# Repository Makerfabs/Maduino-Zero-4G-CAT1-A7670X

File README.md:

# Maduino-Zero-4G-CAT1-A7670X
Maduino Zero 4G LTE CAT1 A7670X

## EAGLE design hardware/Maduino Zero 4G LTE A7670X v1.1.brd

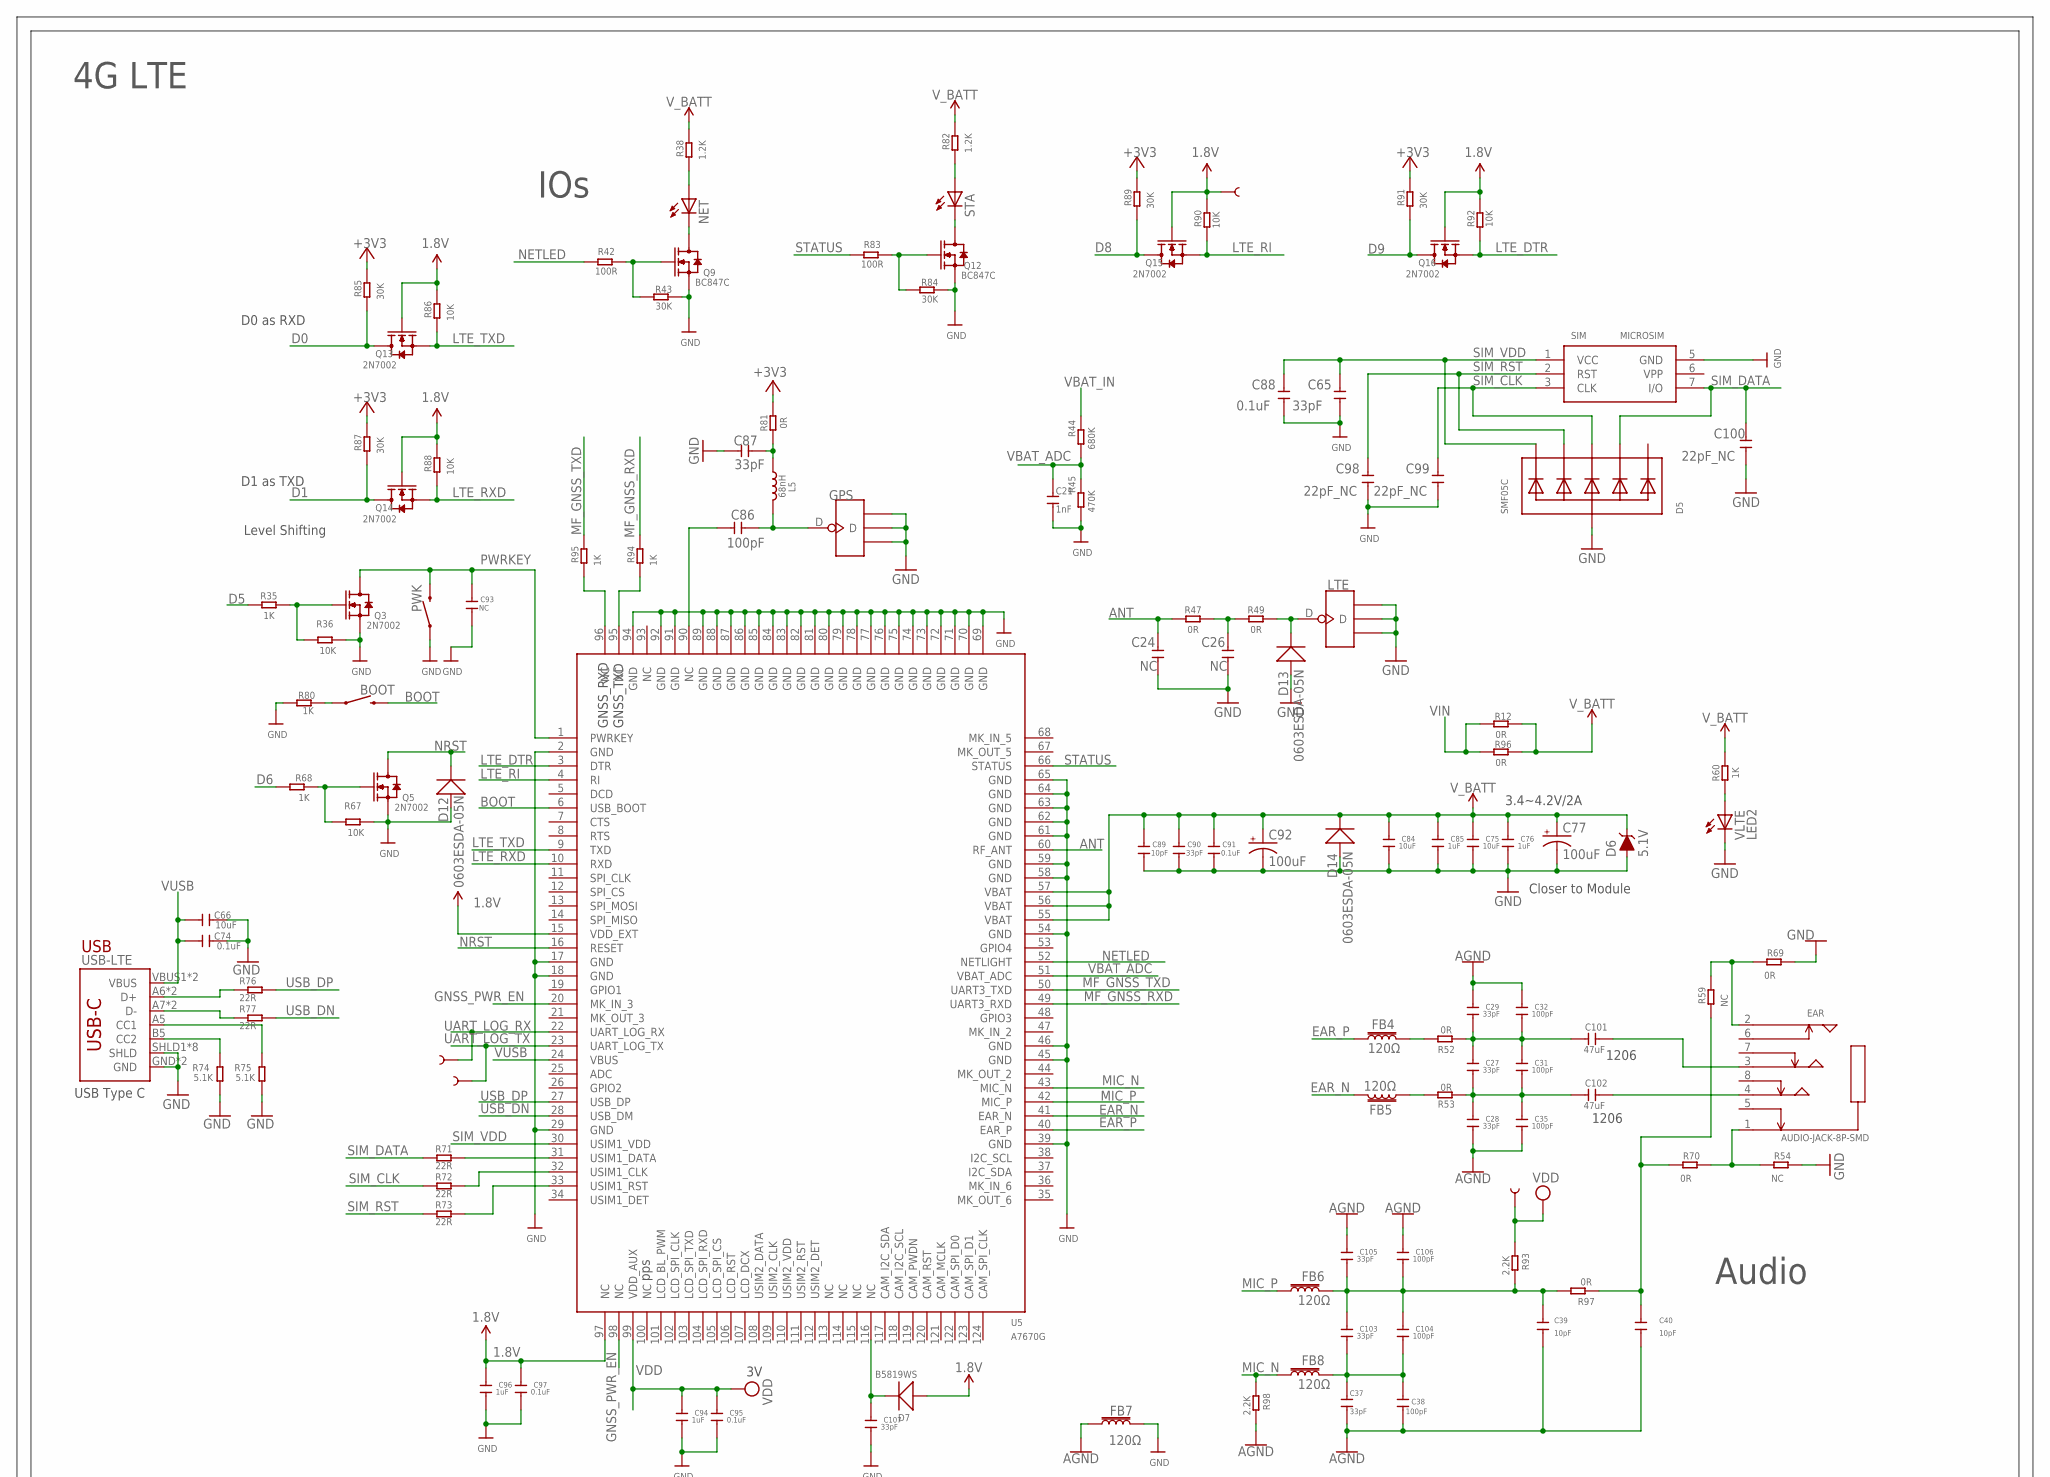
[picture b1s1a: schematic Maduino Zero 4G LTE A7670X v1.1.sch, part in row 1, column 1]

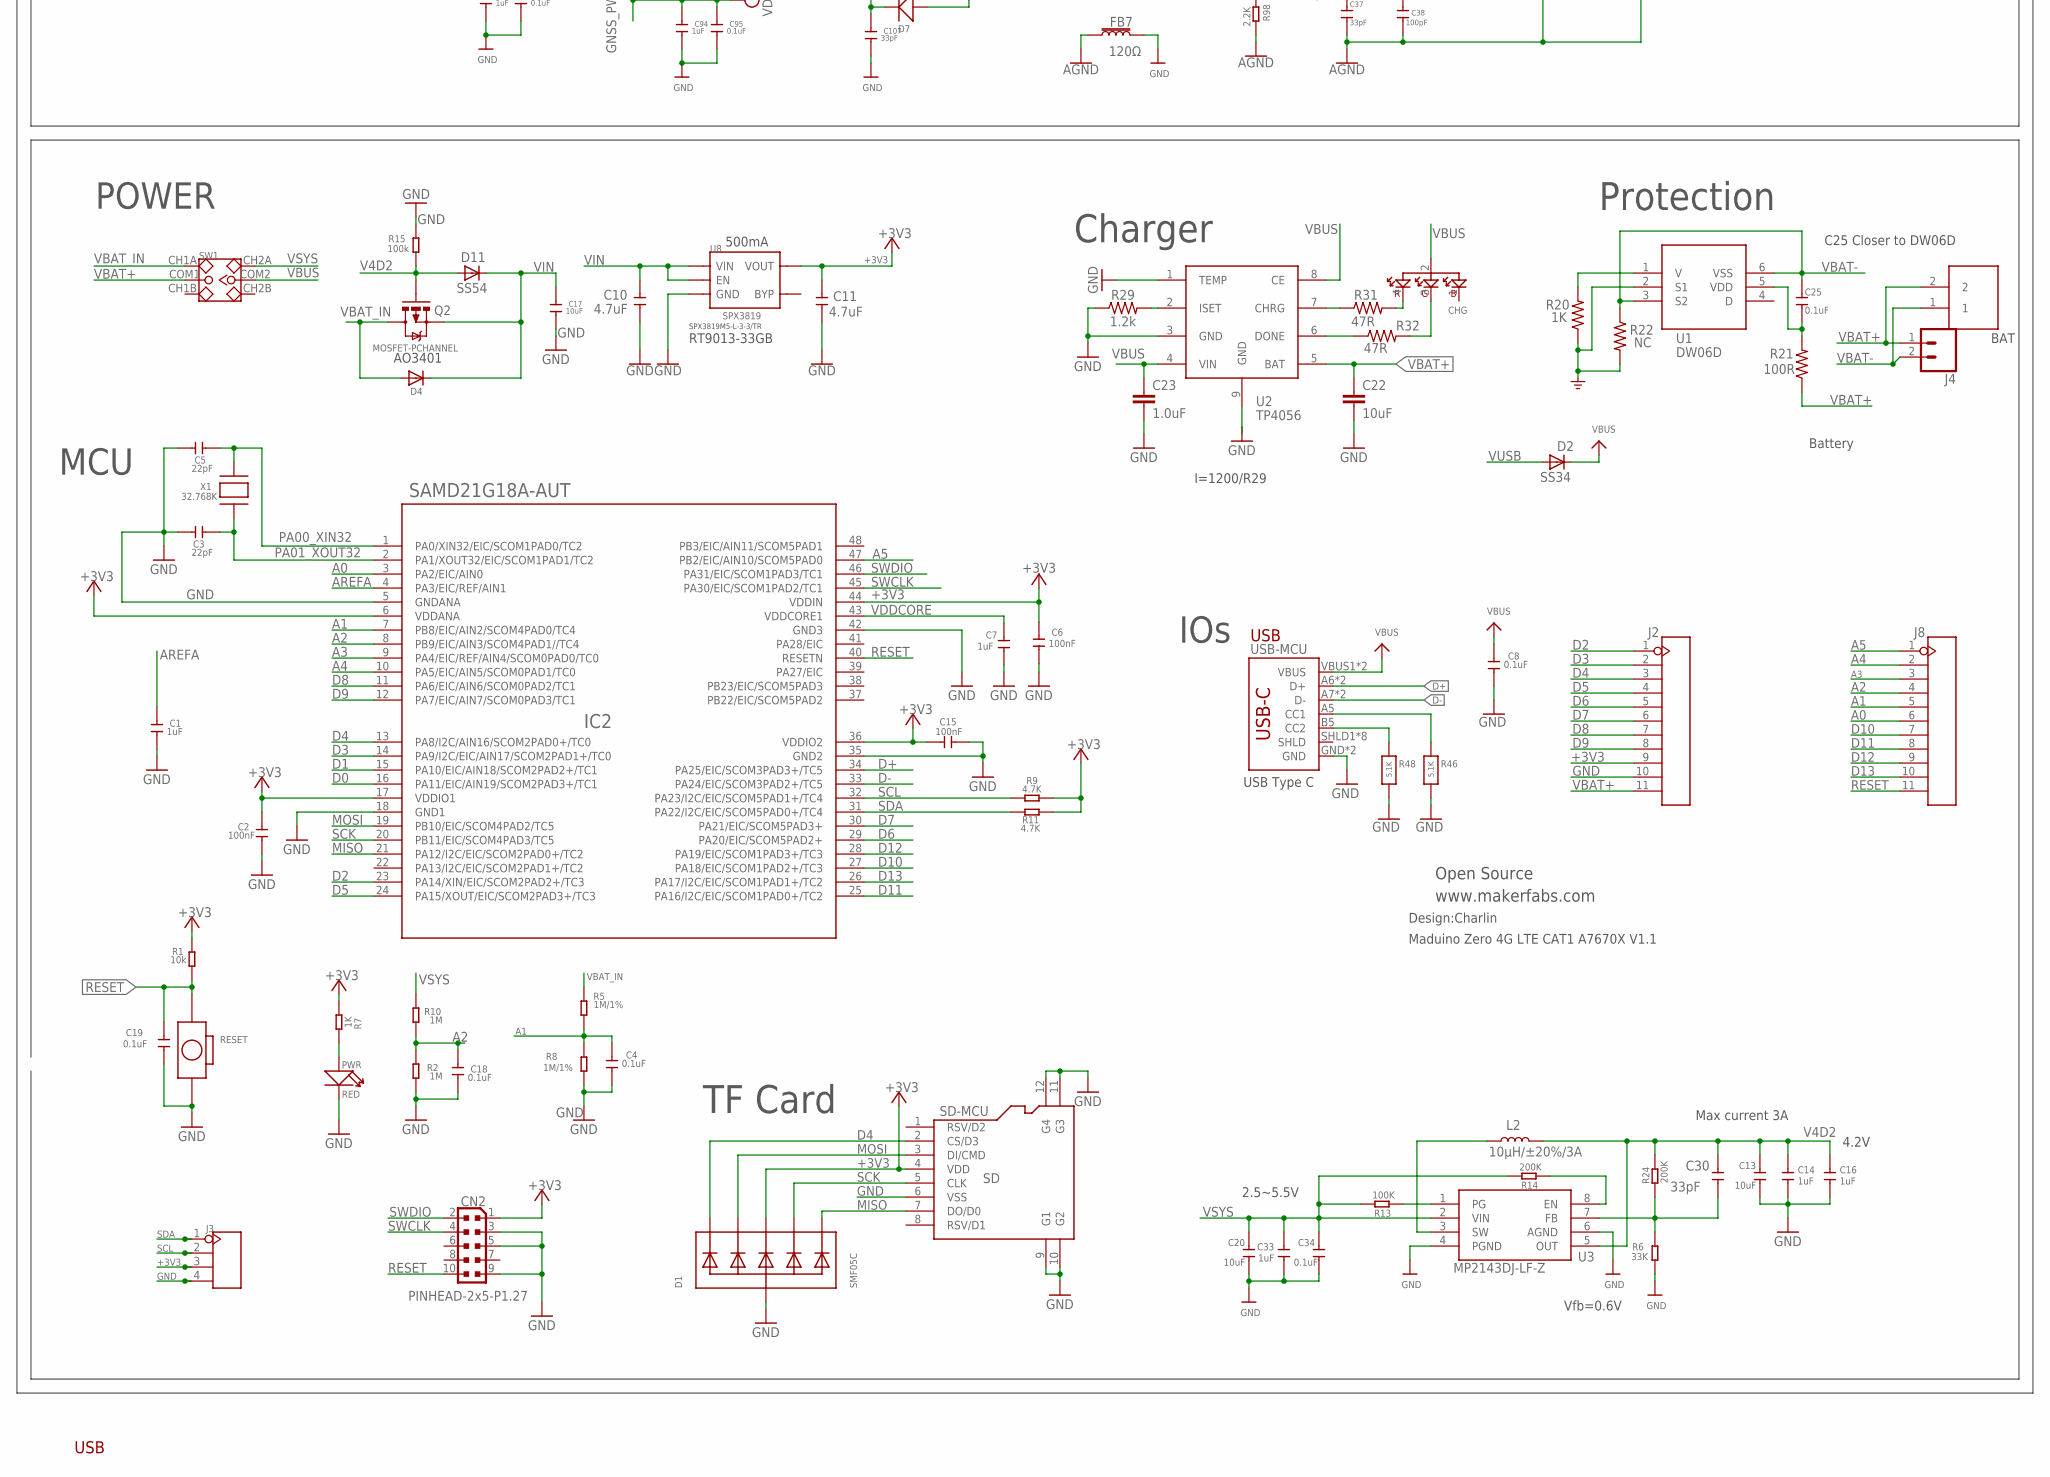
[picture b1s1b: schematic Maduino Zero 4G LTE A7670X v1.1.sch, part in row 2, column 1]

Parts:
BAT: PH2.0-2P-90-DIP
BOOT: MOMENTARY-SWITCH-SPST-SMD-6.0X3.5MM; TACTILE_SWITCH_SMD_6.0X3.5MM
C1, C7, C14, C16, C33, C76, C85, C94, C96: 1uF; 0603
C2, C6, C15: 100nF; 0603
C3, C5: 22pF; 0603
C4, C8, C18, C19, C25, C34, C74, C88, C91, C95, C97: 0.1uF; 0603
C10, C11: 4.7uF; 0603
C13, C17, C20, C22, C66, C75, C84: 10uF; 0603
C21: 1nF; 0603
C23: 1.0uF; 0603
C24, C26, C93: NC; 0603
C27, C28, C29, C30, C37, C65, C87, C90, C103, C105, C107: 33pF; 0603
C31, C32, C35, C38, C86, C104, C106: 100pF; 0603
C39, C40, C89: 10pF; 0603
C77, C92: 100uF; EIA3528
C98, C99, C100: 22pF_NC; 0603
C101, C102: 47uF; DISCRETE_C1206
CHG: E6C0606RGBC3UDA; SMD4-160L160W
CN2: PINHEAD-2x5-P1.27; PINHEAD_2X05_127
D1, D5: SMF05C; SOT363
D2: SS34; DO-214AC
D4: DIODESOD-323F; SOD-323F
D6: 5.1V; SOD-323
D7: B5819WS; SOD323
D11: SS54; DO-214AC
D12, D13, D14: 0603ESDA-05N; DISCRETE_SOD523
EAR: AUDIO-JACK-8P-SMD; AUDIO8P-SMD-3.5-14.5X6.1X4.0MM
FB4, FB5, FB6, FB7, FB8: 120Ω; 0603
GPS: ANTENNA-U-FL; 4P-U-FL
IC2: SAMD21G18A-AUT; TQFP48-7X7
J2, J8: HEADER-11P-2.54; 11P-2.54
J3: HEADER-4P-60/35MILROUND; 4P-65/35ROUND
J4: CONN_02LOCK; 1X02_LOCK
L2: 10µH/±20%/3A; SRN6045
L5: 68nH; L0603
LTE: ANTENNA-U-FL; 4P-U-FL
NET: NET; CHIP-LED0805
PWK: MOMENTARY-SWITCH-SPST-SMD-6.0X3.5MM; TACTILE_SWITCH_SMD_6.0X3.5MM
PWR: RED; LED-0603
Q2: MOSFET-PCHANNEL; SOT23-3
Q3, Q5, Q13, Q14, Q15, Q16: 2N7002; SOT23
Q9, Q12: BC847C; SOT23
R1: 10k; R0603
R2, R10: 1M; R0603
R5, R8: 1M/1%; R0603
R6: 33K; R0603
R7, R35, R60, R68, R80, R94, R95: 1K; R0603
R9, R11: 4.7K; R0603
R12, R47, R49, R52, R53, R69, R70, R81, R96, R97: 0R; R0603
R13: 100K; R0603
R14, R24: 200K; R0603
R15: 100k; R0603
R20: 1K; 0603
R21: 100R; 0603
R22: NC; 0603
R29: 1.2k; 0603
R31, R32: 47R; 0603
R36, R67, R86, R88, R90, R92: 10K; R0603
R38, R82: 1.2K; R0603
R42, R83: 100R; R0603
R43, R84, R85, R87, R89, R91: 30K; R0603
R44: 680K; R0603
R45: 470K; R0603
R46, R48: 5.1K; 0603-NO
R54, R59: NC; R0603
R71, R72, R73, R76, R77: 22R; R0603
R74, R75: 5.1K; R0603
R93, R98: 2.2K; R0603
RESET: BOTTON-2P-90D; 2P-7.62X3.56-90D
SD-MCU: SD; 8P-SMD
SIM: MICROSIM
STA: NET; CHIP-LED0805
SW1: SWITCH-2CH-6P; 6P-2CH-2.54-7.6X3.0
TP1, TP2, TP3, TP6: TEST-POINT3; PAD.03X.03
U1: DW06D; SOT-23-6
U2: TP4056; SOP8-1.27P
U3: MP2143DJ-LF-Z; TSOT23-8
U5: A7670G
U8: SPX3819; SOT23-5
USB-LTE: USB_C5; USB-C-16P-5
USB-MCU: USB_C5; USB-C-16P-5
VLTE: LED2; CHIP-LED0805
X1: 32.768K; XTAL3215

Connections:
1.8V: C96.2, C97.2, D7.+, Q13.1 (G), Q14.1 (G), Q15.1 (G), Q16.1 (G), R86.2, R88.2, R90.2, R92.2, TP6.P$1, U5.15 (VDD_EXT), U5.97 (NC)
+3V3: C2.2, C6.1, C11.2, C15.1, CN2.1, D1.4 (C3), IC2.6 (VDDANA), IC2.17 (VDDIO1), IC2.36 (VDDIO2), IC2.44 (VDDIN), J2.9, J3.3, R1.2, R7.1, R9.2, R11.2, R81.2, R85.2, R87.2, R89.2, R91.2, SD-MCU.4 (VDD), U8.5 (VOUT)
A0: IC2.3 (PA2/EIC/AIN0), J8.6
A1: C4.1, IC2.7 (PB8/EIC/AIN2/SCOM4PAD0/TC4), J8.5, R5.1, R8.2
A2: C18.1, IC2.8 (PB9/EIC/AIN3/SCOM4PAD1//TC4), J8.4, R2.2, R10.1
A3: IC2.9 (PA4/EIC/REF/AIN4/SCOM0PAD0/TC0), J8.3
A4: IC2.10 (PA5/EIC/AIN5/SCOM0PAD1/TC0), J8.2
A5: IC2.47 (PB2/EIC/AIN10/SCOM5PAD0), J8.1
AGND: C28.1, C29.2, C32.2, C35.1, C37.1, C38.1, C39.1, C40.1, C105.2, C106.2, FB7.1, R98.2
ANT: C24.2, R47.1, U5.60 (RF_ANT)
AREFA: C1.1, IC2.4 (PA3/EIC/REF/AIN1)
BOOT: BOOT.2, U5.6 (USB_BOOT)
D0: IC2.16 (PA11/EIC/AIN19/SCOM2PAD3+/TC1), Q13.3 (D), R85.1
D1: IC2.15 (PA10/EIC/AIN18/SCOM2PAD2+/TC1), Q14.3 (D), R87.1
D2: IC2.23 (PA14/XIN/EIC/SCOM2PAD2+/TC3), J2.1
D3: IC2.14 (PA9/I2C/EIC/AIN17/SCOM2PAD1+/TC0), J2.2
D4: D1.1 (C1), IC2.13 (PA8/I2C/AIN16/SCOM2PAD0+/TC0), J2.3, SD-MCU.2 (CS/D3)
D5: IC2.24 (PA15/XOUT/EIC/SCOM2PAD3+/TC3), J2.4, R35.2
D6: IC2.29 (PA20/EIC/SCOM5PAD2+), J2.5, R68.2
D7: IC2.30 (PA21/EIC/SCOM5PAD3+), J2.6
D8: IC2.11 (PA6/EIC/AIN6/SCOM0PAD2/TC1), J2.7, Q15.3 (D), R89.1
D9: IC2.12 (PA7/EIC/AIN7/SCOM0PAD3/TC1), J2.8, Q16.3 (D), R91.1
D10: IC2.27 (PA18/EIC/SCOM1PAD2+/TC3), J8.7
D11: IC2.25 (PA16/I2C/EIC/SCOM1PAD0+/TC2), J8.8
D12: IC2.28 (PA19/EIC/SCOM1PAD3+/TC3), J8.9
D13: IC2.26 (PA17/I2C/EIC/SCOM1PAD1+/TC2), J8.10
D+: IC2.34 (PA25/EIC/SCOM3PAD3+/TC5), USB-MCU.A6 (D+), USB-MCU.B6 (D+)
D-: IC2.33 (PA24/EIC/SCOM3PAD2+/TC5), USB-MCU.A7 (D-), USB-MCU.B7 (D-)
DONE: R32.1, U2.6 (DONE)
EAR_N: FB5.2, U5.41 (EAR_N)
EAR_P: FB4.1, U5.40 (EAR_P)
GND: C1.2, C2.1, C3.2, C4.2, C5.2, C6.2, C7.2, C8.2, C10.1, C11.1, C13.1, C14.1, C15.2, C16.1, C17.1, C18.2, C19.1, C20.1, C21.2, C22.2, C23.2, C24.1, C26.1, C33.1, C34.1, C65.1, C66.2, C74.2, C75.1, C76.1, C77.C (-), C84.1, C85.1, C87.2, C88.1, C89.1, C90.1, C91.1, C92.C (-), C93.1, C94.1, C95.1, C96.1, C97.1, C98.1, C99.1, C100.1, C107.1, CN2.3, CN2.5, CN2.9, D1.2 (A), D5.2 (A), D6.A, D12.+, D13.+, D14.+, FB7.2, GPS.GND1, GPS.GND2, GPS.GND3, IC2.5 (GNDANA), IC2.18 (GND1), IC2.35 (GND2), IC2.42 (GND3), J2.10, J3.4, LTE.GND1, LTE.GND2, LTE.GND3, PWK.1, PWR.-, Q3.2 (S), Q5.2 (S), Q9.2 (S), Q12.2 (S), R2.1, R6.1, R8.1, R15.2, R20.1, R22.2, R29.1, R36.1, R43.1, R45.1, R46.2, R48.2, R54.2, R67.1, R69.2, R74.1, R75.1, R80.2, R84.1, RESET.P$2 (2), SD-MCU.6 (VSS), SD-MCU.9 (G1), SD-MCU.10 (G2), SD-MCU.11 (G3), SD-MCU.12 (G4), SIM.5 (GND), U1.2 (S1), U2.1 (TEMP), U2.3 (GND), U2.9 (GND), U3.4 (PGND), U3.6 (AGND), U5.2 (GND), U5.17 (GND), U5.18 (GND), U5.29 (GND), U5.39 (GND), U5.45 (GND), U5.46 (GND), U5.54 (GND), U5.58 (GND), U5.59 (GND), U5.61 (GND), U5.62 (GND), U5.63 (GND), U5.64 (GND), U5.65 (GND), U5.69 (GND), U5.70 (GND), U5.71 (GND), U5.72 (GND), U5.73 (GND), U5.74 (GND), U5.75 (GND), U5.76 (GND), U5.77 (GND), U5.78 (GND), U5.79 (GND), U5.80 (GND), U5.81 (GND), U5.82 (GND), U5.83 (GND), U5.84 (GND), U5.85 (GND), U5.86 (GND), U5.87 (GND), U5.88 (GND), U5.89 (GND), U5.91 (GND), U5.92 (GND), U5.94 (GND), U8.2 (GND), USB-LTE.GND, USB-LTE.GND2 (GND), USB-LTE.SHLD1 (SHLD), USB-LTE.SHLD2 (SHLD), USB-LTE.SHLD3 (SHLD), USB-LTE.SHLD4 (SHLD), USB-LTE.SHLD5 (SHLD), USB-LTE.SHLD6 (SHLD), USB-LTE.SHLD7 (SHLD), USB-LTE.SHLD8 (SHLD), USB-MCU.GND, USB-MCU.GND2 (GND), VLTE.C
GNSS_PWR_EN: U5.20 (MK_IN_3), U5.98 (NC)
ISET: R29.2, U2.2 (ISET)
LTE_DTR: Q16.2 (S), R92.1, U5.3 (DTR)
LTE_RI: Q15.2 (S), R90.1, U5.4 (RI)
LTE_RXD: Q14.2 (S), R88.1, U5.10 (RXD)
LTE_TXD: Q13.2 (S), R86.1, U5.9 (TXD)
MF_GNSS_RXD: R94.2, U5.49 (UART3_RXD)
MF_GNSS_TXD: R95.2, U5.50 (UART3_TXD)
MIC_N: FB8.1, R98.1, U5.43 (MIC_N)
MIC_P: FB6.1, U5.42 (MIC_P)
MISO: D1.6 (C5), IC2.21 (PA12/I2C/EIC/SCOM2PAD0+/TC2), SD-MCU.7 (DO/D0)
MOSI: D1.3 (C2), IC2.19 (PB10/EIC/SCOM4PAD2/TC5), SD-MCU.3 (DI/CMD)
unnamed: PWR.+, R7.2
unnamed: L2.1, U3.3 (SW)
unnamed: C25.2, R21.2, U1.5 (VDD)
unnamed: R20.2, U1.1 (V)
unnamed: CHG.3, R32.2
unnamed: R31.1, U2.7 (CHRG)
unnamed: R13.1, U3.1 (PG)
unnamed: C30.1, R6.2, R24.1, U3.7 (FB)
unnamed: R14.1, U3.8 (EN)
unnamed: CHG.4, R31.2
unnamed: Q9.1 (G), R42.1, R43.2
unnamed: NET.A, R38.1
unnamed: R46.1, USB-MCU.A5 (CC1)
unnamed: R48.1, USB-MCU.B5 (CC2)
unnamed: NET.C, Q9.3 (D)
unnamed: C26.2, R47.2, R49.1
unnamed: D13.-, LTE.D, R49.2
unnamed: FB4.2, R52.2
unnamed: C101.2, EAR.3
unnamed: C27.1, C28.2, C31.1, C35.2, C102.1, R53.1
unnamed: C40.2, R59.1, R70.1, R97.1
unnamed: C39.2, C103.2, C104.2, C105.1, C106.1, FB6.2, R93.2, R97.2
unnamed: EAR.2, R59.2, R69.1
unnamed: EAR.1, R54.1, R70.2
unnamed: FB5.1, R53.2
unnamed: R71.1, U5.31 (USIM1_DATA)
unnamed: Q3.1 (G), R35.1, R36.2
unnamed: R72.1, U5.32 (USIM1_CLK)
unnamed: R73.1, U5.33 (USIM1_RST)
unnamed: R60.1, VLTE.A
unnamed: R75.2, USB-LTE.A5 (CC1)
unnamed: R74.2, USB-LTE.B5 (CC2)
unnamed: R76.2, USB-LTE.A6 (D+), USB-LTE.B6 (D+)
unnamed: R77.2, USB-LTE.A7 (D-), USB-LTE.B7 (D-)
unnamed: BOOT.1, R80.1
unnamed: C87.1, L5.1, R81.1
unnamed: C86.1, GPS.D, L5.2
unnamed: C86.2, U5.90 (NC)
unnamed: Q12.1 (G), R83.1, R84.2
unnamed: R82.1, STA.A
unnamed: Q5.1 (G), R67.2, R68.1
unnamed: Q12.3 (D), STA.C
unnamed: C27.2, C29.1, C31.2, C32.1, C101.1, R52.1
unnamed: C102.2, EAR.4
unnamed: R94.1, U5.95 (NC)
unnamed: R95.1, U5.96 (NC)
unnamed: C37.2, C38.2, C103.1, C104.1, FB8.2
unnamed: C107.2, D7.-, U5.116 (NC)
NETLED: R42.2, U5.52 (NETLIGHT)
NRST: D12.-, Q5.3 (D), U5.16 (RESET)
PA00_XIN32: C5.1, IC2.1 (PA0/XIN32/EIC/SCOM1PAD0/TC2), X1.P$2
PA01_XOUT32: C3.1, IC2.2 (PA1/XOUT32/EIC/SCOM1PAD1/TC2), X1.P$1
PWRKEY: C93.2, PWK.2, Q3.3 (D), U5.1 (PWRKEY)
RESET: C19.2, CN2.10, IC2.40 (RESETN), J8.11, R1.1, RESET.P$1 (1)
SCK: D1.5 (C4), IC2.20 (PB11/EIC/SCOM4PAD3/TC5), SD-MCU.5 (CLK)
SCL: IC2.32 (PA23/I2C/EIC/SCOM5PAD1+/TC4), J3.2, R9.1
SDA: IC2.31 (PA22/I2C/EIC/SCOM5PAD0+/TC4), J3.1, R11.1
SIM_CLK: C99.2, D5.4 (C3), R72.2, SIM.3 (CLK)
SIM_DATA: C100.2, D5.3 (C2), R71.2, SIM.7 (I/O)
SIM_RST: C98.2, D5.5 (C4), R73.2, SIM.2 (RST)
SIM_VDD: C65.2, C88.2, D5.6 (C5), SIM.1 (VCC), U5.30 (USIM1_VDD)
STATUS: R83.2, U5.66 (STATUS)
SWCLK: CN2.4, IC2.45 (PA30/EIC/SCOM1PAD2/TC1)
SWDIO: CN2.2, IC2.46 (PA31/EIC/SCOM1PAD3/TC1)
UART_LOG_RX: TP3.P$1, U5.22 (UART_LOG_RX)
UART_LOG_TX: TP2.P$1, U5.23 (UART_LOG_TX)
USB_DN: R77.1, U5.28 (USB_DM)
USB_DP: R76.1, U5.27 (USB_DP)
V4D2: C13.2, C14.2, C16.2, C30.2, D11.A, L2.2, Q2.1 (G), R15.1, R24.2, U3.5 (OUT)
VBAT+: BAT.2, C22.1, J2.11, J4.1, R21.1, SW1.COM1, U2.5 (BAT)
VBAT-: BAT.1, C25.1, J4.2, R22.1, U1.3 (S2), U1.6 (VSS)
VBAT_ADC: C21.1, R44.1, R45.2, U5.51 (VBAT_ADC)
VBAT_IN: D4.A, Q2.3 (D), R5.2, R44.2, SW1.CH1A
VBUS: C8.1, C23.1, CHG.2, D2.C, SW1.COM2, U2.4 (VIN), U2.8 (CE), USB-MCU.VBUS1 (VBUS), USB-MCU.VBUS2 (VBUS)
VDD: C94.2, C95.2, R93.1, TP1.P$1, U5.99 (VDD_AUX)
VDDCORE: C7.1, IC2.43 (VDDCORE1)
VIN: C10.2, C17.2, D4.C, D11.C, Q2.2 (S), R12.2, R96.2, U8.1 (VIN), U8.3 (EN)
VSYS: C20.2, C33.2, C34.2, R10.2, R13.2, R14.2, SW1.CH2A, U3.2 (VIN)
VUSB: C66.1, C74.1, D2.A, U5.24 (VBUS), USB-LTE.VBUS1 (VBUS), USB-LTE.VBUS2 (VBUS)
V_BATT: C75.2, C76.2, C77.A (+), C84.2, C85.2, C89.2, C90.2, C91.2, C92.A (+), D6.C, D14.-, R12.1, R38.2, R60.2, R82.2, R96.1, U5.55 (VBAT), U5.56 (VBAT), U5.57 (VBAT)

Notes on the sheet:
500mA
www.makerfabs.com
MCU
IOs
POWER
Design:Charlin
Open Source
AO3401
Maduino Zero 4G LTE CAT1 A7670X V1.1
Battery
C25 Closer to DW06D
Protection
BAT
I=1200/R29
Level Shifting
USB
USB Type C
Audio
Charger
TF Card
D0 as RXD
D1 as TXD
SPX3819M5-L-3-3/TR
RT9013-33GB
Closer to Module
3.4~4.2V/2A
GNSS_TXD
GNSS_RXD
1206
4G LTE
pps
4.2V
Max current 3A
Vfb=0.6V
2.5~5.5V

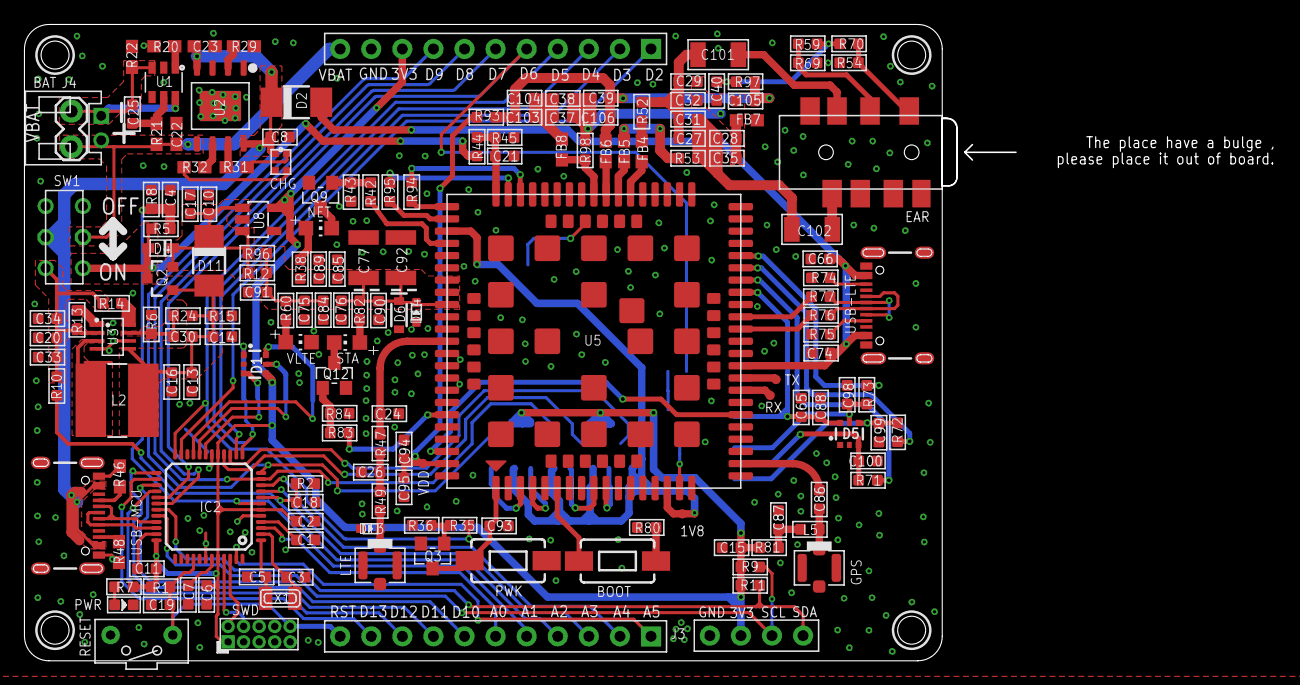
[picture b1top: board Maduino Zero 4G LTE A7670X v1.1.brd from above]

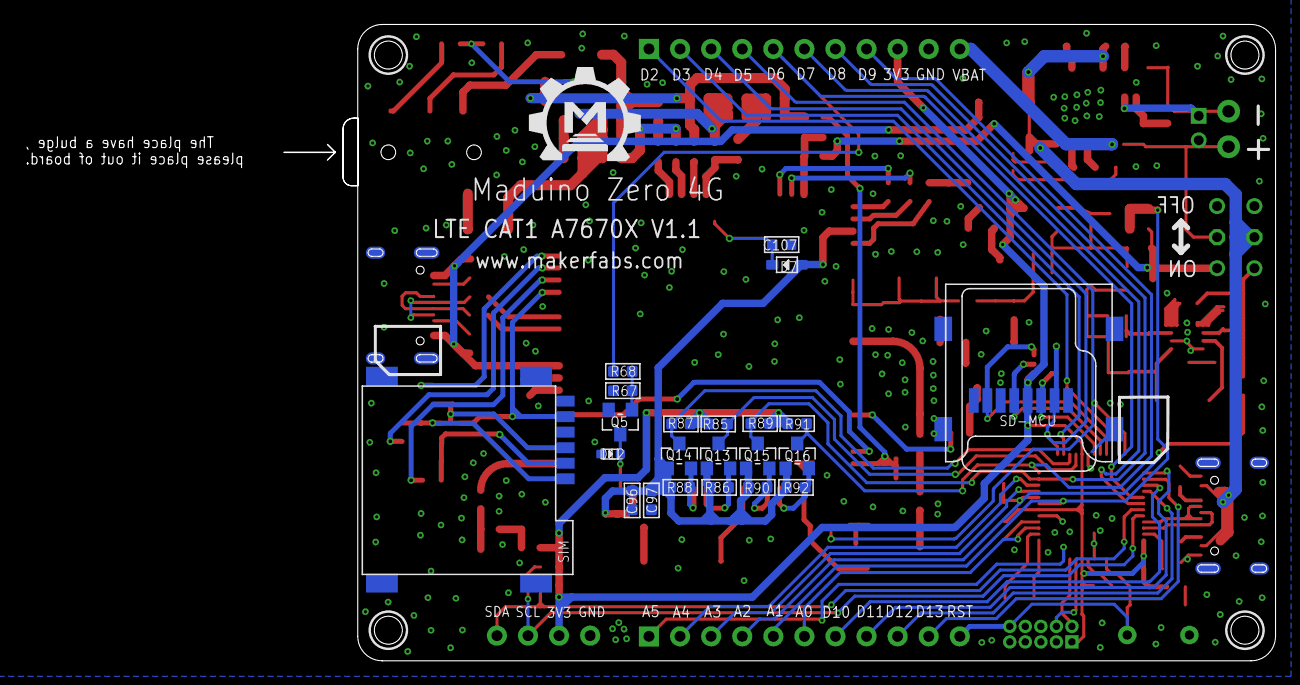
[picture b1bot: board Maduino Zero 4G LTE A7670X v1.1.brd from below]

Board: 2 copper layers, 81.0 x 52.0 mm, 193 parts (23 on the bottom side), 124 nets.

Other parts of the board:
U$1: MAKERFABS_0.3

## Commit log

2023-10-08 Add hardware and example
2023-10-08 Add examples

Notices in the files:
parts and their libraries:
microbuilder: This work is placed in the public domain, and may be freely used for commercial and non-commercial work with the following conditions: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
User-Submitted: Licensing: Creative Commons ShareAlike 4.0 International - https://creativecommons.org/licenses/by-sa/4.0
